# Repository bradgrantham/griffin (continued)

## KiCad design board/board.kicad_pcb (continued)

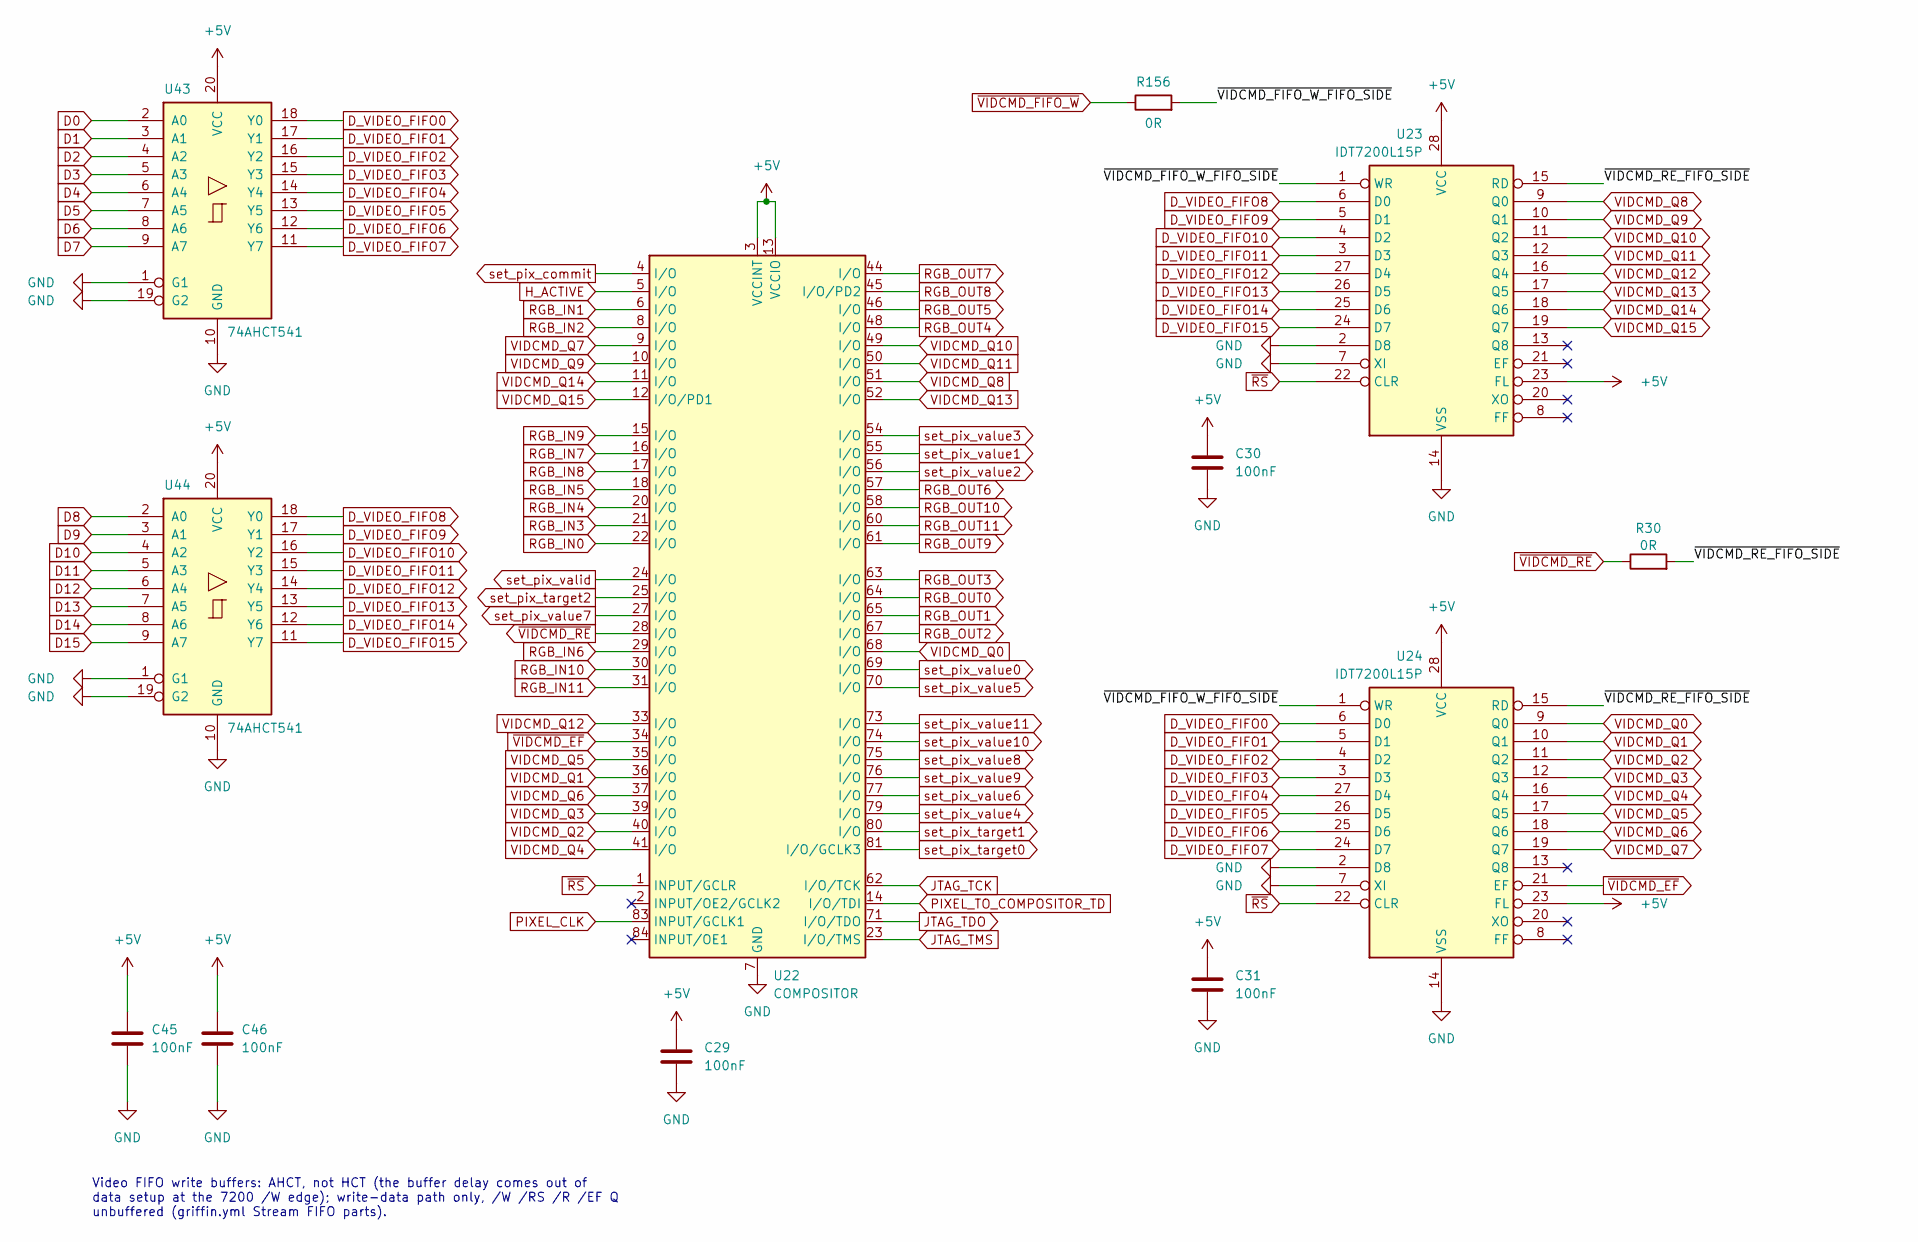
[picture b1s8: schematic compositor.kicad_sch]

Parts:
C29, C30, C31, C45, C46: 100nF; C_Disc_D5.0mm_W2.5mm_P5.00mm
R30, R156: 0R; R_Axial_DIN0207_L6.3mm_D2.5mm_P10.16mm_Horizontal
U22: COMPOSITOR; PLCC-84_THT-Socket
U23, U24: IDT7200L15P; DIP-28_W7.62mm
U43, U44: 74AHCT541; DIP-20_W7.62mm

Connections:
+5V: C29.1, C30.1, C31.1, C45.1, C46.1, U22.3 (VCCINT), U22.13 (VCCIO), U22.26 (VCCIO), U22.38 (VCCIO), U22.43 (VCCINT), U22.53 (VCCIO), U22.66 (VCCIO), U22.78 (VCCIO), U23.23 (FL), U23.28 (VCC), U24.23 (FL), U24.28 (VCC), U43.20 (VCC), U44.20 (VCC); also elsewhere on the board
/COMPOSITOR/~VIDCMD_FIFO_W_FIFO_SIDE: R156.2, U23.1 (WR), U24.1 (WR)
/COMPOSITOR/~VIDCMD_RE_FIFO_SIDE: R30.2, U23.15 (RD), U24.15 (RD)
D0: U43.2 (A0); also elsewhere on the board
D1: U43.3 (A1); also elsewhere on the board
D2: U43.4 (A2); also elsewhere on the board
D3: U43.5 (A3); also elsewhere on the board
D4: U43.6 (A4); also elsewhere on the board
D5: U43.7 (A5); also elsewhere on the board
D6: U43.8 (A6); also elsewhere on the board
D7: U43.9 (A7); also elsewhere on the board
D8: U44.2 (A0); also elsewhere on the board
D9: U44.3 (A1); also elsewhere on the board
D10: U44.4 (A2); also elsewhere on the board
D11: U44.5 (A3); also elsewhere on the board
D12: U44.6 (A4); also elsewhere on the board
D13: U44.7 (A5); also elsewhere on the board
D14: U44.8 (A6); also elsewhere on the board
D15: U44.9 (A7); also elsewhere on the board
D_VIDEO_FIFO0: U24.6 (D0), U43.18 (Y0); also elsewhere on the board
D_VIDEO_FIFO1: U24.5 (D1), U43.17 (Y1); also elsewhere on the board
D_VIDEO_FIFO2: U24.4 (D2), U43.16 (Y2); also elsewhere on the board
D_VIDEO_FIFO3: U24.3 (D3), U43.15 (Y3); also elsewhere on the board
D_VIDEO_FIFO4: U24.27 (D4), U43.14 (Y4); also elsewhere on the board
D_VIDEO_FIFO5: U24.26 (D5), U43.13 (Y5); also elsewhere on the board
D_VIDEO_FIFO6: U24.25 (D6), U43.12 (Y6); also elsewhere on the board
D_VIDEO_FIFO7: U24.24 (D7), U43.11 (Y7); also elsewhere on the board
D_VIDEO_FIFO8: U23.6 (D0), U44.18 (Y0); also elsewhere on the board
D_VIDEO_FIFO9: U23.5 (D1), U44.17 (Y1); also elsewhere on the board
D_VIDEO_FIFO10: U23.4 (D2), U44.16 (Y2); also elsewhere on the board
D_VIDEO_FIFO11: U23.3 (D3), U44.15 (Y3); also elsewhere on the board
D_VIDEO_FIFO12: U23.27 (D4), U44.14 (Y4); also elsewhere on the board
D_VIDEO_FIFO13: U23.26 (D5), U44.13 (Y5); also elsewhere on the board
D_VIDEO_FIFO14: U23.25 (D6), U44.12 (Y6); also elsewhere on the board
D_VIDEO_FIFO15: U23.24 (D7), U44.11 (Y7); also elsewhere on the board
GND: C29.2, C30.2, C31.2, C45.2, C46.2, U22.7 (GND), U22.19 (GND), U22.32 (GND), U22.42 (GND), U22.47 (GND), U22.59 (GND), U22.72 (GND), U22.82 (GND), U23.2 (D8), U23.7 (XI), U23.14 (VSS), U24.2 (D8), U24.7 (XI), U24.14 (VSS), U43.1 (G1), U43.10 (GND), U43.19 (G2), U44.1 (G1), U44.10 (GND), U44.19 (G2); also elsewhere on the board
H_ACTIVE: U22.5 (I/O); also elsewhere on the board
JTAG_TCK: U22.62 (I/O/TCK); also elsewhere on the board
JTAG_TDO: U22.71 (I/O/TDO); also elsewhere on the board
JTAG_TMS: U22.23 (I/O/TMS); also elsewhere on the board
PIXEL_CLK: U22.83 (INPUT/GCLK1); also elsewhere on the board
PIXEL_TO_COMPOSITOR_TD: U22.14 (I/O/TDI); also elsewhere on the board
RGB_IN0: U22.22 (I/O); also elsewhere on the board
RGB_IN1: U22.6 (I/O); also elsewhere on the board
RGB_IN2: U22.8 (I/O); also elsewhere on the board
RGB_IN3: U22.21 (I/O); also elsewhere on the board
RGB_IN4: U22.20 (I/O); also elsewhere on the board
RGB_IN5: U22.18 (I/O); also elsewhere on the board
RGB_IN6: U22.29 (I/O); also elsewhere on the board
RGB_IN7: U22.16 (I/O); also elsewhere on the board
RGB_IN8: U22.17 (I/O); also elsewhere on the board
RGB_IN9: U22.15 (I/O); also elsewhere on the board
RGB_IN10: U22.30 (I/O); also elsewhere on the board
RGB_IN11: U22.31 (I/O); also elsewhere on the board
RGB_OUT0: U22.64 (I/O); also elsewhere on the board
RGB_OUT1: U22.65 (I/O); also elsewhere on the board
RGB_OUT2: U22.67 (I/O); also elsewhere on the board
RGB_OUT3: U22.63 (I/O); also elsewhere on the board
RGB_OUT4: U22.48 (I/O); also elsewhere on the board
RGB_OUT5: U22.46 (I/O); also elsewhere on the board
RGB_OUT6: U22.57 (I/O); also elsewhere on the board
RGB_OUT7: U22.44 (I/O); also elsewhere on the board
RGB_OUT8: U22.45 (I/O/PD2); also elsewhere on the board
RGB_OUT9: U22.61 (I/O); also elsewhere on the board
RGB_OUT10: U22.58 (I/O); also elsewhere on the board
RGB_OUT11: U22.60 (I/O); also elsewhere on the board
VIDCMD_Q0: U22.68 (I/O), U24.9 (Q0)
VIDCMD_Q1: U22.36 (I/O), U24.10 (Q1)
VIDCMD_Q2: U22.40 (I/O), U24.11 (Q2)
VIDCMD_Q3: U22.39 (I/O), U24.12 (Q3)
VIDCMD_Q4: U22.41 (I/O), U24.16 (Q4)
VIDCMD_Q5: U22.35 (I/O), U24.17 (Q5)
VIDCMD_Q6: U22.37 (I/O), U24.18 (Q6)
VIDCMD_Q7: U22.9 (I/O), U24.19 (Q7)
VIDCMD_Q8: U22.51 (I/O), U23.9 (Q0)
VIDCMD_Q9: U22.10 (I/O), U23.10 (Q1)
VIDCMD_Q10: U22.49 (I/O), U23.11 (Q2)
VIDCMD_Q11: U22.50 (I/O), U23.12 (Q3)
VIDCMD_Q12: U22.33 (I/O), U23.16 (Q4)
VIDCMD_Q13: U22.52 (I/O), U23.17 (Q5)
VIDCMD_Q14: U22.11 (I/O), U23.18 (Q6)
VIDCMD_Q15: U22.12 (I/O/PD1), U23.19 (Q7)
set_pix_commit: U22.4 (I/O); also elsewhere on the board
set_pix_target0: U22.81 (I/O/GCLK3); also elsewhere on the board
set_pix_target1: U22.80 (I/O); also elsewhere on the board
set_pix_target2: U22.25 (I/O); also elsewhere on the board
set_pix_valid: U22.24 (I/O); also elsewhere on the board
set_pix_value0: U22.69 (I/O); also elsewhere on the board
set_pix_value1: U22.55 (I/O); also elsewhere on the board
set_pix_value2: U22.56 (I/O); also elsewhere on the board
set_pix_value3: U22.54 (I/O); also elsewhere on the board
set_pix_value4: U22.79 (I/O); also elsewhere on the board
set_pix_value5: U22.70 (I/O); also elsewhere on the board
set_pix_value6: U22.77 (I/O); also elsewhere on the board
set_pix_value7: U22.27 (I/O); also elsewhere on the board
set_pix_value8: U22.75 (I/O); also elsewhere on the board
set_pix_value9: U22.76 (I/O); also elsewhere on the board
set_pix_value10: U22.74 (I/O); also elsewhere on the board
set_pix_value11: U22.73 (I/O); also elsewhere on the board
~RS: U22.1 (INPUT/GCLR), U23.22 (CLR), U24.22 (CLR); also elsewhere on the board
~VIDCMD_EF: U22.34 (I/O), U24.21 (EF)
~VIDCMD_FIFO_W: R156.1; also elsewhere on the board
~VIDCMD_RE: R30.1, U22.28 (I/O)

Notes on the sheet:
Video FIFO write buffers: AHCT, not HCT (the buffer delay comes out of data setup at the 7200 /W edge); write-data path only, /W /RS /R /EF Q unbuffered (griffin.yml Stream FIFO parts).

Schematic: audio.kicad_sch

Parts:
C40, C41, C50, C51: 100nF; C_Disc_D5.0mm_W2.5mm_P5.00mm
R39, R157: 0R; R_Axial_DIN0207_L6.3mm_D2.5mm_P10.16mm_Horizontal
TP7: TestPoint; TestPoint_Pad_D1.5mm
U28: AUDIO; PLCC-84_THT-Socket
U29: IDT7200L15P; DIP-28_W7.62mm
U45, U46: 74AHCT541; DIP-20_W7.62mm

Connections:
+5V: C40.1, C41.1, C50.1, C51.1, U28.3 (VCCINT), U28.13 (VCCIO), U28.26 (VCCIO), U28.38 (VCCIO), U28.43 (VCCINT), U28.53 (VCCIO), U28.66 (VCCIO), U28.78 (VCCIO), U29.23 (FL), U29.28 (VCC), U45.20 (VCC), U46.20 (VCC); also elsewhere on the board
/AUDIO/~AUDCTL_FIFO_W_FIFO_SIDE: R157.2, U29.1 (WR)
AUDIO_TO_ENGINE_TD: U28.71 (I/O/TDO); also elsewhere on the board
CONTROL_Q0: U28.31 (I/O), U29.9 (Q0)
CONTROL_Q1: U28.30 (I/O), U29.10 (Q1)
CONTROL_Q2: U28.25 (I/O), U29.11 (Q2)
CONTROL_Q3: U28.41 (I/O), U29.12 (Q3)
CONTROL_Q4: U28.40 (I/O), U29.16 (Q4)
CONTROL_Q5: U28.39 (I/O), U29.17 (Q5)
CONTROL_Q6: U28.37 (I/O), U29.18 (Q6)
CONTROL_Q7: U28.35 (I/O), U29.19 (Q7)
D0: U45.2 (A0); also elsewhere on the board
D1: U45.3 (A1); also elsewhere on the board
D2: U45.4 (A2); also elsewhere on the board
D3: U45.5 (A3); also elsewhere on the board
D4: U45.6 (A4); also elsewhere on the board
D5: U45.7 (A5); also elsewhere on the board
D6: U45.8 (A6); also elsewhere on the board
D7: U45.9 (A7); also elsewhere on the board
D8: U46.2 (A0); also elsewhere on the board
D9: U46.3 (A1); also elsewhere on the board
D10: U46.4 (A2); also elsewhere on the board
D11: U46.5 (A3); also elsewhere on the board
D12: U46.6 (A4); also elsewhere on the board
D13: U46.7 (A5); also elsewhere on the board
D14: U46.8 (A6); also elsewhere on the board
D15: U46.9 (A7); also elsewhere on the board
D_AUDIO_FIFO0: U29.6 (D0), U45.18 (Y0); also elsewhere on the board
D_AUDIO_FIFO1: U29.5 (D1), U45.17 (Y1); also elsewhere on the board
D_AUDIO_FIFO2: U29.4 (D2), U45.16 (Y2); also elsewhere on the board
D_AUDIO_FIFO3: U29.3 (D3), U45.15 (Y3); also elsewhere on the board
D_AUDIO_FIFO4: U29.27 (D4), U45.14 (Y4); also elsewhere on the board
D_AUDIO_FIFO5: U29.26 (D5), U45.13 (Y5); also elsewhere on the board
D_AUDIO_FIFO6: U29.25 (D6), U45.12 (Y6); also elsewhere on the board
D_AUDIO_FIFO7: U29.24 (D7), U45.11 (Y7); also elsewhere on the board
D_AUDIO_FIFO8: U46.18 (Y0); also elsewhere on the board
D_AUDIO_FIFO9: U46.17 (Y1); also elsewhere on the board
D_AUDIO_FIFO10: U46.16 (Y2); also elsewhere on the board
D_AUDIO_FIFO11: U46.15 (Y3); also elsewhere on the board
D_AUDIO_FIFO12: U46.14 (Y4); also elsewhere on the board
D_AUDIO_FIFO13: U46.13 (Y5); also elsewhere on the board
D_AUDIO_FIFO14: U46.12 (Y6); also elsewhere on the board
D_AUDIO_FIFO15: U46.11 (Y7); also elsewhere on the board
GATE0: U28.15 (I/O); also elsewhere on the board
GATE1: U28.24 (I/O); also elsewhere on the board
GATE2: U28.33 (I/O); also elsewhere on the board
GATE3: U28.4 (I/O); also elsewhere on the board
GND: C40.2, C41.2, C50.2, C51.2, U28.7 (GND), U28.19 (GND), U28.32 (GND), U28.42 (GND), U28.47 (GND), U28.59 (GND), U28.72 (GND), U28.82 (GND), U29.2 (D8), U29.7 (XI), U29.14 (VSS), U45.1 (G1), U45.10 (GND), U45.19 (G2), U46.1 (G1), U46.10 (GND), U46.19 (G2); also elsewhere on the board
HBLANK: U28.12 (I/O/PD1); also elsewhere on the board
JTAG_TCK: U28.62 (I/O/TCK); also elsewhere on the board
JTAG_TMS: U28.23 (I/O/TMS); also elsewhere on the board
unnamed: R39.1, U29.15 (RD)
PIXEL_CLK: U28.83 (INPUT/GCLK1); also elsewhere on the board
PORTS_TO_AUDIO_TD: U28.14 (I/O/TDI); also elsewhere on the board
~AUDCTL_FIFO_W: R157.1; also elsewhere on the board
~CONTROL_EF: TP7.1, U28.11 (I/O), U29.21 (EF)
~CONTROL_R: R39.2, U28.81 (I/O/GCLK3)
~RESET: U28.22 (I/O), U29.22 (CLR); also elsewhere on the board
~SAMPLE_EF0: U28.9 (I/O); also elsewhere on the board
~SAMPLE_EF1: U28.8 (I/O); also elsewhere on the board
~SAMPLE_EF2: U28.6 (I/O); also elsewhere on the board
~SAMPLE_EF3: U28.10 (I/O); also elsewhere on the board
~SAMPLE_R0: U28.16 (I/O); also elsewhere on the board
~SAMPLE_R1: U28.27 (I/O); also elsewhere on the board
~SAMPLE_R2: U28.34 (I/O); also elsewhere on the board
~SAMPLE_R3: U28.5 (I/O); also elsewhere on the board

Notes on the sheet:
Audio FIFO write buffers U45, U46: AHCT, not HCT; write-data path only (griffin.yml Stream FIFO parts). The main bus does not run to the audio section.

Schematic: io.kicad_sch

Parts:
C18: 100nF; C_Disc_D5.0mm_W2.5mm_P5.00mm
C34, C35: 33pF; C_Disc_D3.0mm_W1.6mm_P2.50mm
J3: FTDI serial A; PinHeader_1x06_P2.54mm_Vertical
J12: FTDI serial B; PinHeader_1x06_P2.54mm_Vertical
R100, R101, R102, R103: 1k; R_Axial_DIN0207_L6.3mm_D2.5mm_P10.16mm_Horizontal
U27: 68C681
Y5: 3.6864MHz; Resonator-2Pin_W10.0mm_H5.0mm

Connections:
+5V: C18.1, U27.37 (IACKN), U27.40 (VCC); also elsewhere on the board
GND: C18.2, C34.2, C35.1, J3.1, J12.1, U27.20 (GND); also elsewhere on the board
HDR_RTS_A: J3.6, R102.1
HDR_RTS_B: J12.6, R103.1
HDR_TXD_A: J3.4, R100.1
HDR_TXD_B: J12.4, R101.1
unnamed: C35.2, U27.32 (X1/CLK), Y5.1
unnamed: C34.1, U27.33 (X2), Y5.2
UART_RX_A: R100.2, U27.31 (RXDA); also elsewhere on the board
UART_RX_B: R101.2, U27.10 (RXDB); also elsewhere on the board
UART_TX_A: J3.5, U27.30 (TXDA); also elsewhere on the board
UART_TX_B: J12.5, U27.11 (TXDB); also elsewhere on the board
~CTS_A: R102.2, U27.7 (IP0); also elsewhere on the board
~CTS_B: R103.2, U27.4 (IP1); also elsewhere on the board
~RTS_A: J3.2, U27.29 (OP0); also elsewhere on the board
~RTS_B: J12.2, U27.12 (OP1); also elsewhere on the board

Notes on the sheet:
TTL headers: FTDI TTL-232R pinout. Header TXD and RTS reach the DUART through 1k so a stuffed MAX232 wins any collision (griffin.yml RS-232 entry).

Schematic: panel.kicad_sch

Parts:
C90, C91: 10nF film; C_Rect_L7.2mm_W2.5mm_P5.00mm
D4, D5, D6, D7, D8, D9, D10, D11, D12, D13, D14, D15, D16, D17, D18, D19, D20, D21, D22, D23, D24, D25, D26, D27, D28, D29, D30, D31: 1N4148; D_DO-35_SOD27_P7.62mm_Horizontal
F1, F2: 0.5A polyfuse; Fuse_Bourns_MF-RHT050
J4: KEYBOARD; Mini_din6
J5: MOUSE; Mini_din6
J10, J11: DIN-5_180degree
J20: JOYSTICK 1; DSUB-9_Pins_Horizontal_P2.77x2.84mm_EdgePinOffset4.94mm_Hou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
J21: JOYSTICK 2; DSUB-9_Pins_Horizontal_P2.77x2.84mm_EdgePinOffset4.94mm_Hou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
Q3, Q4: 2N7000; TO-92_Inline
R120, R121, R122, R123, R124, R125, R126, R127, R128, R129, R130, R131, R132, R133: 100R; R_Axial_DIN0207_L6.3mm_D2.5mm_P10.16mm_Horizontal
R134, R135: 1M; R_Axial_DIN0207_L6.3mm_D2.5mm_P10.16mm_Horizontal
R136: 10k; R_Axial_DIN0207_L6.3mm_D2.5mm_P10.16mm_Horizontal
RN1, RN2: 10k bussed; R_Array_SIP7

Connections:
+5V: D4.1 (K), D6.1 (K), D8.1 (K), D10.1 (K), D12.1 (K), D14.1 (K), D16.1 (K), D18.1 (K), D20.1 (K), D22.1 (K), D24.1 (K), D26.1 (K), D28.1 (K), D30.1 (K), F1.1, F2.1, J4.4, J5.4, J10.5, J11.5, R134.1, R135.1, R136.1, RN1.1 (common), RN2.1 (common); also elsewhere on the board
/PANEL/JS1_1: D4.2 (A), D5.1 (K), J20.1, R120.1
/PANEL/JS1_2: D6.2 (A), D7.1 (K), J20.2, R121.1
/PANEL/JS1_3: D8.2 (A), D9.1 (K), J20.3, R122.1
/PANEL/JS1_4: D10.2 (A), D11.1 (K), J20.4, R123.1
/PANEL/JS1_5: D14.2 (A), D15.1 (K), J20.5, R125.1
/PANEL/JS1_6: D12.2 (A), D13.1 (K), J20.6, R124.1
/PANEL/JS1_7: F1.2, J20.7
/PANEL/JS1_9: D16.2 (A), D17.1 (K), J20.9, R126.1
/PANEL/JS2_1: D18.2 (A), D19.1 (K), J21.1, R127.1
/PANEL/JS2_2: D20.2 (A), D21.1 (K), J21.2, R128.1
/PANEL/JS2_3: D22.2 (A), D23.1 (K), J21.3, R129.1
/PANEL/JS2_4: D24.2 (A), D25.1 (K), J21.4, R130.1
/PANEL/JS2_5: D28.2 (A), D29.1 (K), J21.5, R132.1
/PANEL/JS2_6: D26.2 (A), D27.1 (K), J21.6, R131.1
/PANEL/JS2_7: F2.2, J21.7
/PANEL/JS2_9: D30.2 (A), D31.1 (K), J21.9, R133.1
GND: C90.2, C91.2, D5.2 (A), D7.2 (A), D9.2 (A), D11.2 (A), D13.2 (A), D15.2 (A), D17.2 (A), D19.2 (A), D21.2 (A), D23.2 (A), D25.2 (A), D27.2 (A), D29.2 (A), D31.2 (A), J4.3, J4.7 (GND), J5.3, J5.7 (GND), J10.4, J11.4, J20.8, J21.8, Q3.1 (S), Q4.1 (S); also elsewhere on the board
JOYSTICK_1_DOWN: R121.2, RN1.3 (R2); also elsewhere on the board
JOYSTICK_1_FIRE: R124.2, RN1.6 (R5); also elsewhere on the board
JOYSTICK_1_LEFT: R122.2, RN1.4 (R3); also elsewhere on the board
JOYSTICK_1_PIN5: C91.1, Q4.3 (D), R125.2, R135.2; also elsewhere on the board
JOYSTICK_1_PIN9: C90.1, Q3.3 (D), R126.2, R134.2; also elsewhere on the board
JOYSTICK_1_RIGHT: R123.2, RN1.5 (R4); also elsewhere on the board
JOYSTICK_1_UP: R120.2, RN1.2 (R1); also elsewhere on the board
JOYSTICK_2_DOWN: R128.2, RN2.3 (R2); also elsewhere on the board
JOYSTICK_2_FIRE: R131.2, RN2.6 (R5); also elsewhere on the board
JOYSTICK_2_LEFT: R129.2, RN2.4 (R3); also elsewhere on the board
JOYSTICK_2_PIN5: R132.2, R136.2; also elsewhere on the board
JOYSTICK_2_PIN9: R133.2, RN2.7 (R6); also elsewhere on the board
JOYSTICK_2_RIGHT: R130.2, RN2.5 (R4); also elsewhere on the board
JOYSTICK_2_UP: R127.2, RN2.2 (R1); also elsewhere on the board
PADDLE_DUMP: Q3.2 (G), Q4.2 (G); also elsewhere on the board
PS2_CLK: J4.5, J10.1; also elsewhere on the board
PS2_DATA: J4.1, J10.2; also elsewhere on the board
PS2_MOUSE_CLK: J5.5, J11.1; also elsewhere on the board
PS2_MOUSE_DATA: J5.1, J11.2; also elsewhere on the board

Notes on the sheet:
Atari DE-9: 1 up, 2 down, 3 left, 4 right, 5/9 paddle pots (SMS button 2 on 9), 6 fire, 7 +5V (polyfuse), 8 GND. Port 1 hosts the paddles: 1M pull-ups on 5/9 (the pot parallels the pull-up), 10 nF ramp caps, 2N7000 dump FETs on PADDLE_DUMP; DNP the caps/FETs for a sticks-only build.
ESD: 100R series + 1N4148 clamps to +5V/GND on every switch line, connector side. Values 100R, 1N4148, 10k, 1M, 10 nF and 0.5 A are assumptions; griffin.md gives only the topology.

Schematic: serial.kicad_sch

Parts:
C70, C71, C72, C73, C74, C75, C76, C77, C78, C79: 1uF; CP_Radial_D5.0mm_P2.00mm
C83: 100nF; C_Disc_D5.0mm_W2.5mm_P5.00mm
J18: CONSOLE DB-25F DCE; DSUB-25_Socket_Horizontal_P2.77x2.84mm_EdgePinOffset7.70mm_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
J19: MODEM DB-25M DTE; DSUB-25_Pins_Horizontal_P2.77x2.84mm_EdgePinOffset7.70mm_Ho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
R104, R105, R106, R107, R108, R109: 10k; R_Axial_DIN0207_L6.3mm_D2.5mm_P10.16mm_Horizontal
U36, U37: MAX232; DIP-16_W7.62mm
U38: SN75189; DIP-14_W7.62mm

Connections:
+5V: C74.1, C79.1, C83.1, R104.1, R105.1, R106.1, R107.1, R108.1, R109.1, U36.16 (VCC), U37.16 (VCC), U38.14 (VCC); also elsewhere on the board
/SERIAL/CONSOLE_DTR: J18.6, J18.8, J18.20
/SERIAL/MAXA_C1+: C70.1, U36.1 (C1+)
/SERIAL/MAXA_C1-: C70.2, U36.3 (C1-)
/SERIAL/MAXA_C2+: C71.1, U36.4 (C2+)
/SERIAL/MAXA_C2-: C71.2, U36.5 (C2-)
/SERIAL/MAXA_VS+: C72.1, U36.2 (VS+)
/SERIAL/MAXA_VS-: C73.2, U36.6 (VS-)
/SERIAL/MAXB_C1+: C75.1, U37.1 (C1+)
/SERIAL/MAXB_C1-: C75.2, U37.3 (C1-)
/SERIAL/MAXB_C2+: C76.1, U37.4 (C2+)
/SERIAL/MAXB_C2-: C76.2, U37.5 (C2-)
/SERIAL/MAXB_VS+: C77.1, U37.2 (VS+)
/SERIAL/MAXB_VS-: C78.2, U37.6 (VS-)
/SERIAL/MODEM_DTR: J19.6, J19.20
/SERIAL/RS232_A_CTS: J18.5, U36.7 (T2OUT)
/SERIAL/RS232_A_RTS: J18.4, U36.8 (R2IN)
/SERIAL/RS232_A_RXD: J18.3, U36.14 (T1OUT)
/SERIAL/RS232_A_TXD: J18.2, U36.13 (R1IN)
/SERIAL/RS232_B_CTS: J19.5, U37.8 (R2IN)
/SERIAL/RS232_B_DCD: J19.8, U38.1 (1A)
/SERIAL/RS232_B_RI: J19.22, U38.4 (2A)
/SERIAL/RS232_B_RTS: J19.4, U37.7 (T2OUT)
/SERIAL/RS232_B_RXD: J19.3, U37.13 (R1IN)
/SERIAL/RS232_B_TXD: J19.2, U37.14 (T1OUT)
DCD_B: R108.2, U38.3 (1Y)
GND: C72.2, C73.1, C74.2, C77.2, C78.1, C79.2, C83.2, J18.7, J19.7, U36.15 (GND), U37.15 (GND), U38.7 (GND), U38.10 (3A), U38.13 (4A); also elsewhere on the board
RI_B: R109.2, U38.6 (2Y)
UART_RX_A: R104.2, U36.12 (R1OUT); also elsewhere on the board
UART_RX_B: R105.2, U37.12 (R1OUT); also elsewhere on the board
UART_TX_A: U36.11 (T1IN); also elsewhere on the board
UART_TX_B: U37.11 (T1IN); also elsewhere on the board
~CTS_A: R106.2, U36.9 (R2OUT); also elsewhere on the board
~CTS_B: R107.2, U37.9 (R2OUT); also elsewhere on the board
~RTS_A: U36.10 (T2IN); also elsewhere on the board
~RTS_B: U37.10 (T2IN); also elsewhere on the board

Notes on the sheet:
RS-232 level stages (griffin.yml interfaces, RS-232 level stage). Ch A console: DB-25 female wired DCE; terminal TXD (2) and RTS (4) are received, TXDA and ~RTS_A drive pins 3 (RXD) and 5 (CTS); DSR (6) and DCD (8) strapped to the terminal DTR (20). Ch B modem: DB-25 male wired DTE; TXDB -> 2, 3 ->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

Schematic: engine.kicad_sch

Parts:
C25: 100nF; C_Disc_D5.0mm_W2.5mm_P5.00mm
U18: ENGINE; PLCC-84_THT-Socket

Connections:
+5V: C25.1, U18.3 (VCCINT), U18.13 (VCCIO), U18.26 (VCCIO), U18.38 (VCCIO), U18.43 (VCCINT), U18.53 (VCCIO), U18.66 (VCCIO), U18.78 (VCCIO); also elsewhere on the board
A1: U18.56 (I/O); also elsewhere on the board
A2: U18.57 (I/O); also elsewhere on the board
A3: U18.58 (I/O); also elsewhere on the board
A4: U18.44 (I/O); also elsewhere on the board
A5: U18.60 (I/O); also elsewhere on the board
A6: U18.61 (I/O); also elsewhere on the board
A7: U18.45 (I/O/PD2); also elsewhere on the board
A8: U18.46 (I/O); also elsewhere on the board
A9: U18.48 (I/O); also elsewhere on the board
A10: U18.50 (I/O); also elsewhere on the board
A11: U18.49 (I/O); also elsewhere on the board
A12: U18.51 (I/O); also elsewhere on the board
A13: U18.52 (I/O); also elsewhere on the board
A14: U18.55 (I/O); also elsewhere on the board
A15: U18.54 (I/O); also elsewhere on the board
A16: U18.67 (I/O); also elsewhere on the board
A17: U18.81 (I/O/GCLK3); also elsewhere on the board
A18: U18.65 (I/O); also elsewhere on the board
A19: U18.64 (I/O); also elsewhere on the board
A20: U18.70 (I/O); also elsewhere on the board
A21: U18.68 (I/O); also elsewhere on the board
A22: U18.69 (I/O); also elsewhere on the board
A23: U18.28 (I/O); also elsewhere on the board
AUDIO_TO_ENGINE_TD: U18.14 (I/O/TDI); also elsewhere on the board
D0: U18.17 (I/O); also elsewhere on the board
D1: U18.75 (I/O); also elsewhere on the board
D2: U18.22 (I/O); also elsewhere on the board
D3: U18.6 (I/O); also elsewhere on the board
D4: U18.15 (I/O); also elsewhere on the board
D5: U18.5 (I/O); also elsewhere on the board
D6: U18.4 (I/O); also elsewhere on the board
D7: U18.16 (I/O); also elsewhere on the board
D8: U18.73 (I/O); also elsewhere on the board
D9: U18.8 (I/O); also elsewhere on the board
D10: U18.9 (I/O); also elsewhere on the board
D11: U18.10 (I/O); also elsewhere on the board
D12: U18.11 (I/O); also elsewhere on the board
D13: U18.12 (I/O/PD1); also elsewhere on the board
D14: U18.74 (I/O); also elsewhere on the board
D15: U18.20 (I/O); also elsewhere on the board
ENGINE_ACTIVE: U18.30 (I/O); also elsewhere on the board
ENGINE_TO_PIXEL_TD: U18.71 (I/O/TDO); also elsewhere on the board
ENGINE_WAITING: U18.31 (I/O); also elsewhere on the board
FC0: U18.77 (I/O); also elsewhere on the board
FC1: U18.76 (I/O); also elsewhere on the board
FC2: U18.25 (I/O); also elsewhere on the board
GND: C25.2, U18.7 (GND), U18.19 (GND), U18.32 (GND), U18.42 (GND), U18.47 (GND), U18.59 (GND), U18.72 (GND), U18.82 (GND); also elsewhere on the board
HBLANK: U18.2 (INPUT/OE2/GCLK2); also elsewhere on the board
JTAG_TCK: U18.62 (I/O/TCK); also elsewhere on the board
JTAG_TMS: U18.23 (I/O/TMS); also elsewhere on the board
R/~W: U18.27 (I/O); also elsewhere on the board
SYSCLK: U18.83 (INPUT/GCLK1); also elsewhere on the board
~AS: U18.80 (I/O); also elsewhere on the board
~AUDCTL_FIFO_W: U18.37 (I/O); also elsewhere on the board
~BGACK: U18.29 (I/O); also elsewhere on the board
~BG: U18.21 (I/O); also elsewhere on the board
~BR: U18.24 (I/O); also elsewhere on the board
~ENGINE_IRQ: U18.33 (I/O); also elsewhere on the board
~ENGINE_SELECT: U18.18 (I/O); also elsewhere on the board
~LDS: U18.63 (I/O); also elsewhere on the board
~PIXELS_FIFO_W: U18.34 (I/O); also elsewhere on the board
~RESET: U18.1 (INPUT/GCLR); also elsewhere on the board
~SAMPLES0_FIFO_W: U18.35 (I/O); also elsewhere on the board
~SAMPLES1_FIFO_W: U18.40 (I/O); also elsewhere on the board
~SAMPLES2_FIFO_W: U18.41 (I/O); also elsewhere on the board
~SAMPLES3_FIFO_W: U18.39 (I/O); also elsewhere on the board
~UDS: U18.79 (I/O); also elsewhere on the board
~VIDCMD_FIFO_W: U18.36 (I/O); also elsewhere on the board

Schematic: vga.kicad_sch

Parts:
C47, C48: 100nF; C_Disc_D5.0mm_W2.5mm_P5.00mm
J22: DE-15 VGA; AMPHENOL_ICD15S13E4GX00LF
R50, R51, R52, R53, R54, R57, R58, R59, R60, R61, R64, R65, R66, R67, R68: 1k; R_Axial_DIN0207_L6.3mm_D2.5mm_P10.16mm_Horizontal
R55, R62, R69: 3.9k; R_Axial_DIN0207_L6.3mm_D2.5mm_P10.16mm_Horizontal
R56, R63, R70, R71, R72: 100R; R_Axial_DIN0207_L6.3mm_D2.5mm_P10.16mm_Horizontal
U47, U48: 74AC541; DIP-20_W7.62mm

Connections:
+5V: C47.1, C48.1, U47.20 (VCC), U48.20 (VCC); also elsewhere on the board
/VGA_OUT/HS_BUF: R71.1, U48.14 (Y4)
/VGA_OUT/HS_OUT: J22.13, R71.2
/VGA_OUT/VB0: R69.1, U48.15 (Y3)
/VGA_OUT/VB1: R67.1, U48.16 (Y2)
/VGA_OUT/VB1_MID: R67.2, R68.1
/VGA_OUT/VB2: R66.1, U48.17 (Y1)
/VGA_OUT/VB3: R64.1, R65.1, U48.18 (Y0)
/VGA_OUT/VG0: R62.1, U47.11 (Y7)
/VGA_OUT/VG1: R60.1, U47.12 (Y6)
/VGA_OUT/VG1_MID: R60.2, R61.1
/VGA_OUT/VG2: R59.1, U47.13 (Y5)
/VGA_OUT/VG3: R57.1, R58.1, U47.14 (Y4)
/VGA_OUT/VGA_B: J22.3, R64.2, R65.2, R66.2, R68.2, R69.2, R70.1
/VGA_OUT/VGA_G: J22.2, R57.2, R58.2, R59.2, R61.2, R62.2, R63.1
/VGA_OUT/VGA_R: J22.1, R50.2, R51.2, R52.2, R54.2, R55.2, R56.1
/VGA_OUT/VR0: R55.1, U47.15 (Y3)
/VGA_OUT/VR1: R53.1, U47.16 (Y2)
/VGA_OUT/VR1_MID: R53.2, R54.1
/VGA_OUT/VR2: R52.1, U47.17 (Y1)
/VGA_OUT/VR3: R50.1, R51.1, U47.18 (Y0)
/VGA_OUT/VS_BUF: R72.1, U48.13 (Y5)
/VGA_OUT/VS_OUT: J22.14, R72.2
GND: C47.2, C48.2, J22.5, J22.6, J22.7, J22.8, J22.10, J22.S1 (SHIELD), J22.S2 (SHIELD__1), R56.2, R63.2, R70.2, U47.1 (G1), U47.10 (GND), U47.19 (G2), U48.1 (G1), U48.8 (A6), U48.9 (A7), U48.10 (GND), U48.19 (G2); also elsewhere on the board
RGB_OUT0: U48.5 (A3); also elsewhere on the board
RGB_OUT1: U48.4 (A2); also elsewhere on the board
RGB_OUT2: U48.3 (A1); also elsewhere on the board
RGB_OUT3: U48.2 (A0); also elsewhere on the board
RGB_OUT4: U47.9 (A7); also elsewhere on the board
RGB_OUT5: U47.8 (A6); also elsewhere on the board
RGB_OUT6: U47.7 (A5); also elsewhere on the board
RGB_OUT7: U47.6 (A4); also elsewhere on the board
RGB_OUT8: U47.5 (A3); also elsewhere on the board
RGB_OUT9: U47.4 (A2); also elsewhere on the board
RGB_OUT10: U47.3 (A1); also elsewhere on the board
RGB_OUT11: U47.2 (A0); also elsewhere on the board
VGA_HSYNC: U48.6 (A4); also elsewhere on the board
VGA_VSYNC: U48.7 (A5); also elsewhere on the board

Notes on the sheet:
Ladders and shunts at the DE-15, not at the buffers; 12 DAC traces short and matched (griffin.yml VGA entry). yml BOM says 21x 1k; this topology uses 15.

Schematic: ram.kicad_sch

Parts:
C6, C7, C8, C9, C10, C11, C12, C13: 100nF; C_Disc_D5.0mm_W2.5mm_P5.00mm
U5: RAM 1 LO; DIP-32_W15.24mm
U6: RAM 1 HI; DIP-32_W15.24mm
U7: RAM 2 LO; DIP-32_W15.24mm
U8: RAM 2 HI; DIP-32_W15.24mm
U9: RAM 3 LO; DIP-32_W15.24mm
U10: RAM 3 HI; DIP-32_W15.24mm
U11: RAM 4 LO; DIP-32_W15.24mm
U12: RAM 4 HI; DIP-32_W15.24mm

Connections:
+5V: C6.1, C7.1, C8.1, C9.1, C10.1, C11.1, C12.1, C13.1, U5.32 (VCC), U6.32 (VCC), U7.32 (VCC), U8.32 (VCC), U9.32 (VCC), U10.32 (VCC), U11.32 (VCC), U12.32 (VCC); also elsewhere on the board
A1: U5.12 (A0), U6.12 (A0), U7.12 (A0), U8.12 (A0), U9.12 (A0), U10.12 (A0), U11.12 (A0), U12.12 (A0); also elsewhere on the board
A2: U5.11 (A1), U6.11 (A1), U7.11 (A1), U8.11 (A1), U9.11 (A1), U10.11 (A1), U11.11 (A1), U12.11 (A1); also elsewhere on the board
A3: U5.10 (A2), U6.10 (A2), U7.10 (A2), U8.10 (A2), U9.10 (A2), U10.10 (A2), U11.10 (A2), U12.10 (A2); also elsewhere on the board
A4: U5.9 (A3), U6.9 (A3), U7.9 (A3), U8.9 (A3), U9.9 (A3), U10.9 (A3), U11.9 (A3), U12.9 (A3); also elsewhere on the board
A5: U5.8 (A4), U6.8 (A4), U7.8 (A4), U8.8 (A4), U9.8 (A4), U10.8 (A4), U11.8 (A4), U12.8 (A4); also elsewhere on the board
A6: U5.7 (A5), U6.7 (A5), U7.7 (A5), U8.7 (A5), U9.7 (A5), U10.7 (A5), U11.7 (A5), U12.7 (A5); also elsewhere on the board
A7: U5.6 (A6), U6.6 (A6), U7.6 (A6), U8.6 (A6), U9.6 (A6), U10.6 (A6), U11.6 (A6), U12.6 (A6); also elsewhere on the board
A8: U5.5 (A7), U6.5 (A7), U7.5 (A7), U8.5 (A7), U9.5 (A7), U10.5 (A7), U11.5 (A7), U12.5 (A7); also elsewhere on the board
A9: U5.27 (A8), U6.27 (A8), U7.27 (A8), U8.27 (A8), U9.27 (A8), U10.27 (A8), U11.27 (A8), U12.27 (A8); also elsewhere on the board
A10: U5.26 (A9), U6.26 (A9), U7.26 (A9), U8.26 (A9), U9.26 (A9), U10.26 (A9), U11.26 (A9), U12.26 (A9); also elsewhere on the board
A11: U5.23 (A10), U6.23 (A10), U7.23 (A10), U8.23 (A10), U9.23 (A10), U10.23 (A10), U11.23 (A10), U12.23 (A10); also elsewhere on the board
A12: U5.25 (A11), U6.25 (A11), U7.25 (A11), U8.25 (A11), U9.25 (A11), U10.25 (A11), U11.25 (A11), U12.25 (A11); also elsewhere on the board
A13: U5.4 (A12), U6.4 (A12), U7.4 (A12), U8.4 (A12), U9.4 (A12), U10.4 (A12), U11.4 (A12), U12.4 (A12); also elsewhere on the board
A14: U5.28 (A13), U6.28 (A13), U7.28 (A13), U8.28 (A13), U9.28 (A13), U10.28 (A13), U11.28 (A13), U12.28 (A13); also elsewhere on the board
A15: U5.3 (A14), U6.3 (A14), U7.3 (A14), U8.3 (A14), U9.3 (A14), U10.3 (A14), U11.3 (A14), U12.3 (A14); also elsewhere on the board
A16: U5.31 (A15), U6.31 (A15), U7.31 (A15), U8.31 (A15), U9.31 (A15), U10.31 (A15), U11.31 (A15), U12.31 (A15); also elsewhere on the board
A17: U5.2 (A16), U6.2 (A16), U7.2 (A16), U8.2 (A16), U9.2 (A16), U10.2 (A16), U11.2 (A16), U12.2 (A16); also elsewhere on the board
A18: U5.30 (A17), U6.30 (A17), U7.30 (A17), U8.30 (A17), U9.30 (A17), U10.30 (A17), U11.30 (A17), U12.30 (A17); also elsewhere on the board
A19: U5.1 (A18), U6.1 (A18), U7.1 (A18), U8.1 (A18), U9.1 (A18), U10.1 (A18), U11.1 (A18), U12.1 (A18); also elsewhere on the board
D0: U5.13 (DQ0), U7.13 (DQ0), U9.13 (DQ0), U11.13 (DQ0); also elsewhere on the board
D1: U5.14 (DQ1), U7.14 (DQ1), U9.14 (DQ1), U11.14 (DQ1); also elsewhere on the board
D2: U5.15 (DQ2), U7.15 (DQ2), U9.15 (DQ2), U11.15 (DQ2); also elsewhere on the board
D3: U5.17 (DQ3), U7.17 (DQ3), U9.17 (DQ3), U11.17 (DQ3); also elsewhere on the board
D4: U5.18 (DQ4), U7.18 (DQ4), U9.18 (DQ4), U11.18 (DQ4); also elsewhere on the board
D5: U5.19 (DQ5), U7.19 (DQ5), U9.19 (DQ5), U11.19 (DQ5); also elsewhere on the board
D6: U5.20 (DQ6), U7.20 (DQ6), U9.20 (DQ6), U11.20 (DQ6); also elsewhere on the board
D7: U5.21 (DQ7), U7.21 (DQ7), U9.21 (DQ7), U11.21 (DQ7); also elsewhere on the board
D8: U6.13 (DQ0), U8.13 (DQ0), U10.13 (DQ0), U12.13 (DQ0); also elsewhere on the board
D9: U6.14 (DQ1), U8.14 (DQ1), U10.14 (DQ1), U12.14 (DQ1); also elsewhere on the board
D10: U6.15 (DQ2), U8.15 (DQ2), U10.15 (DQ2), U12.15 (DQ2); also elsewhere on the board
D11: U6.17 (DQ3), U8.17 (DQ3), U10.17 (DQ3), U12.17 (DQ3); also elsewhere on the board
D12: U6.18 (DQ4), U8.18 (DQ4), U10.18 (DQ4), U12.18 (DQ4); also elsewhere on the board
D13: U6.19 (DQ5), U8.19 (DQ5), U10.19 (DQ5), U12.19 (DQ5); also elsewhere on the board
D14: U6.20 (DQ6), U8.20 (DQ6), U10.20 (DQ6), U12.20 (DQ6); also elsewhere on the board
D15: U6.21 (DQ7), U8.21 (DQ7), U10.21 (DQ7), U12.21 (DQ7); also elsewhere on the board
GND: C6.2, C7.2, C8.2, C9.2, C10.2, C11.2, C12.2, C13.2, U5.16 (VSS), U5.24 (OE#), U6.16 (VSS), U6.24 (OE#), U7.16 (VSS), U7.24 (OE#), U8.16 (VSS), U8.24 (OE#), U9.16 (VSS), U9.24 (OE#), U10.16 (VSS), U10.24 (OE#), U11.16 (VSS), U11.24 (OE#), U12.16 (VSS), U12.24 (OE#); also elsewhere on the board
~RAM_SELECT_1: U5.22 (CE#), U6.22 (CE#); also elsewhere on the board
~RAM_SELECT_2: U7.22 (CE#), U8.22 (CE#); also elsewhere on the board
~RAM_SELECT_3: U9.22 (CE#), U10.22 (CE#); also elsewhere on the board
~RAM_SELECT_4: U11.22 (CE#), U12.22 (CE#); also elsewhere on the board
~WRITE_HI: U6.29 (WE#), U8.29 (WE#), U10.29 (WE#), U12.29 (WE#); also elsewhere on the board
~WRITE_LO: U5.29 (WE#), U7.29 (WE#), U9.29 (WE#), U11.29 (WE#); also elsewhere on the board
